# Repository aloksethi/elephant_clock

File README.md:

# elephant_clock
four digit clock

## Hardware
* two 7-seg displays for hours and two 7-seg displays for minutes.
* two switches along with debounce ckt.
* one green LED in middle of hours and minutes segments.
* rpi-pico is the brains.

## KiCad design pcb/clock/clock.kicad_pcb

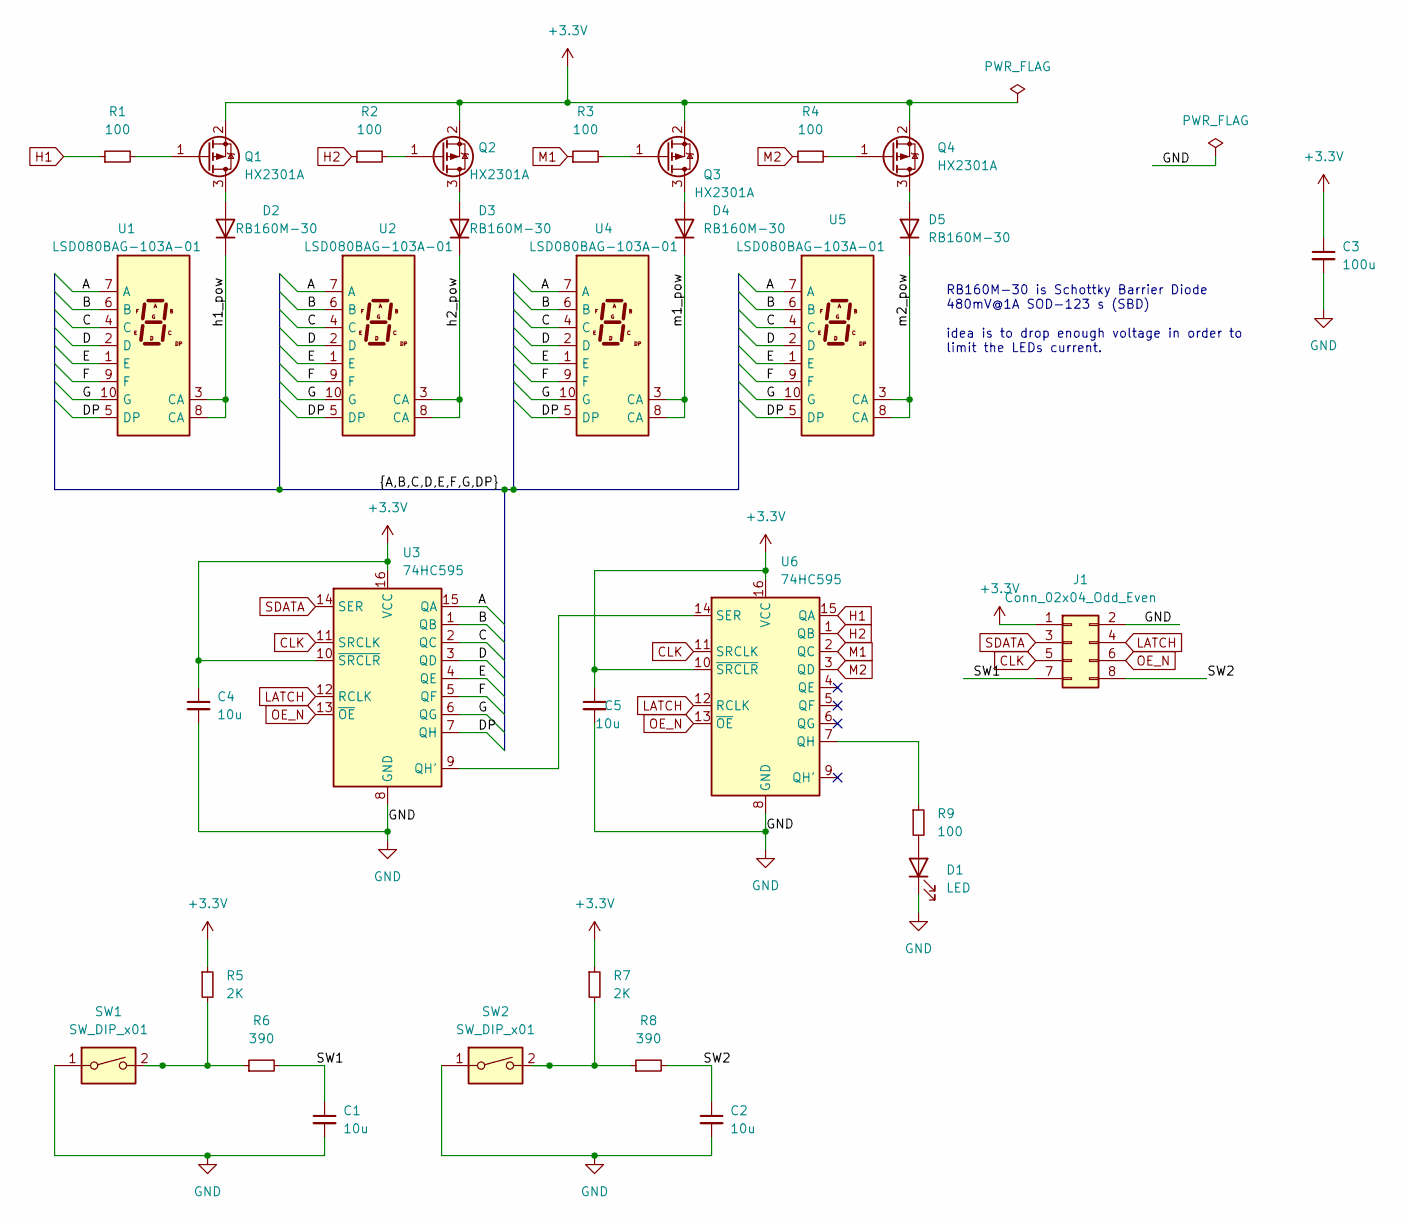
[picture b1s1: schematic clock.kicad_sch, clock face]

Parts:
C1, C2, C4, C5: 10u; C_0805_2012Metric_Pad1.18x1.45mm_HandSolder
C3: 100u; CP_Elec_8x10.5
D1: LED; LED_0805_2012Metric_Pad1.15x1.40mm_HandSolder
D2, D3, D4, D5: RB160M-30; D_SOD-123
J1: Conn_02x04_Odd_Even; PinHeader_2x04_P2.54mm_Vertical_SMD
Q1, Q2, Q3, Q4: HX2301A; SOT-23_Handsoldering
R1, R2, R3, R4: 100; R_0603_1608Metric_Pad0.98x0.95mm_HandSolder
R5, R7: 2K; R_0805_2012Metric_Pad1.20x1.40mm_HandSolder
R6, R8: 390; R_0805_2012Metric_Pad1.20x1.40mm_HandSolder
R9: 100; R_0805_2012Metric_Pad1.20x1.40mm_HandSolder
SW1, SW2: SW_DIP_x01; SW_SPST_lcsc_c174049
U1, U2, U4, U5: LSD080BAG-103A-01; 7SegmentLED_lsd080bag-103a
U3: 74HC595; SOIC-16_3.9x9.9mm_P1.27mm_handsolder
U6: 74HC595; SOIC-16_3.9x9.9mm_P1.27mm

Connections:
+3V3: C3.1, C4.1, C5.1, J1.1, Q1.2 (S), Q2.2 (S), Q3.2 (S), Q4.2 (S), R5.1, R7.1, U3.10 (~SRCLR), U3.16 (VCC), U6.10 (~SRCLR), U6.16 (VCC)
/A: U1.7 (A), U2.7 (A), U3.15 (QA), U4.7 (A), U5.7 (A)
/B: U1.6 (B), U2.6 (B), U3.1 (QB), U4.6 (B), U5.6 (B)
/C: U1.4 (C), U2.4 (C), U3.2 (QC), U4.4 (C), U5.4 (C)
/D: U1.2 (D), U2.2 (D), U3.3 (QD), U4.2 (D), U5.2 (D)
/DP: U1.5 (DP), U2.5 (DP), U3.7 (QH), U4.5 (DP), U5.5 (DP)
/E: U1.1 (E), U2.1 (E), U3.4 (QE), U4.1 (E), U5.1 (E)
/F: U1.9 (F), U2.9 (F), U3.5 (QF), U4.9 (F), U5.9 (F)
/G: U1.10 (G), U2.10 (G), U3.6 (QG), U4.10 (G), U5.10 (G)
/SW1: C1.1, J1.7, R6.2
/SW2: C2.1, J1.8, R8.2
/h1_pow: D2.1 (K), U1.3 (CA), U1.8 (CA)
/h2_pow: D3.1 (K), U2.3 (CA), U2.8 (CA)
/m1_pow: D4.1 (K), U4.3 (CA), U4.8 (CA)
/m2_pow: D5.1 (K), U5.3 (CA), U5.8 (CA)
CLK: J1.5, U3.11 (SRCLK), U6.11 (SRCLK)
GND: C1.2, C2.2, C3.2, C4.2, C5.2, D1.1 (K), J1.2, SW1.1, SW2.1, U3.8 (GND), U6.8 (GND)
H1: R1.1, U6.15 (QA)
H2: R2.1, U6.1 (QB)
LATCH: J1.4, U3.12 (RCLK), U6.12 (RCLK)
M1: R3.1, U6.2 (QC)
M2: R4.1, U6.3 (QD)
unnamed: D1.2 (A), R9.2
unnamed: Q1.1 (G), R1.2
unnamed: D2.2 (A), Q1.3 (D)
unnamed: Q2.1 (G), R2.2
unnamed: D3.2 (A), Q2.3 (D)
unnamed: Q3.1 (G), R3.2
unnamed: D4.2 (A), Q3.3 (D)
unnamed: Q4.1 (G), R4.2
unnamed: D5.2 (A), Q4.3 (D)
unnamed: R5.2, R6.1, SW1.2
unnamed: R7.2, R8.1, SW2.2
unnamed: R9.1, U6.7 (QH)
unnamed: U3.9 (QH'), U6.14 (SER)
OE_N: J1.6, U3.13 (~OE), U6.13 (~OE)
SDATA: J1.3, U3.14 (SER)

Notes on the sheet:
RB160M-30 is Schottky Barrier Diode 480mV@1A SOD-123 s (SBD) idea is to drop enough voltage in order to limit the LEDs current.

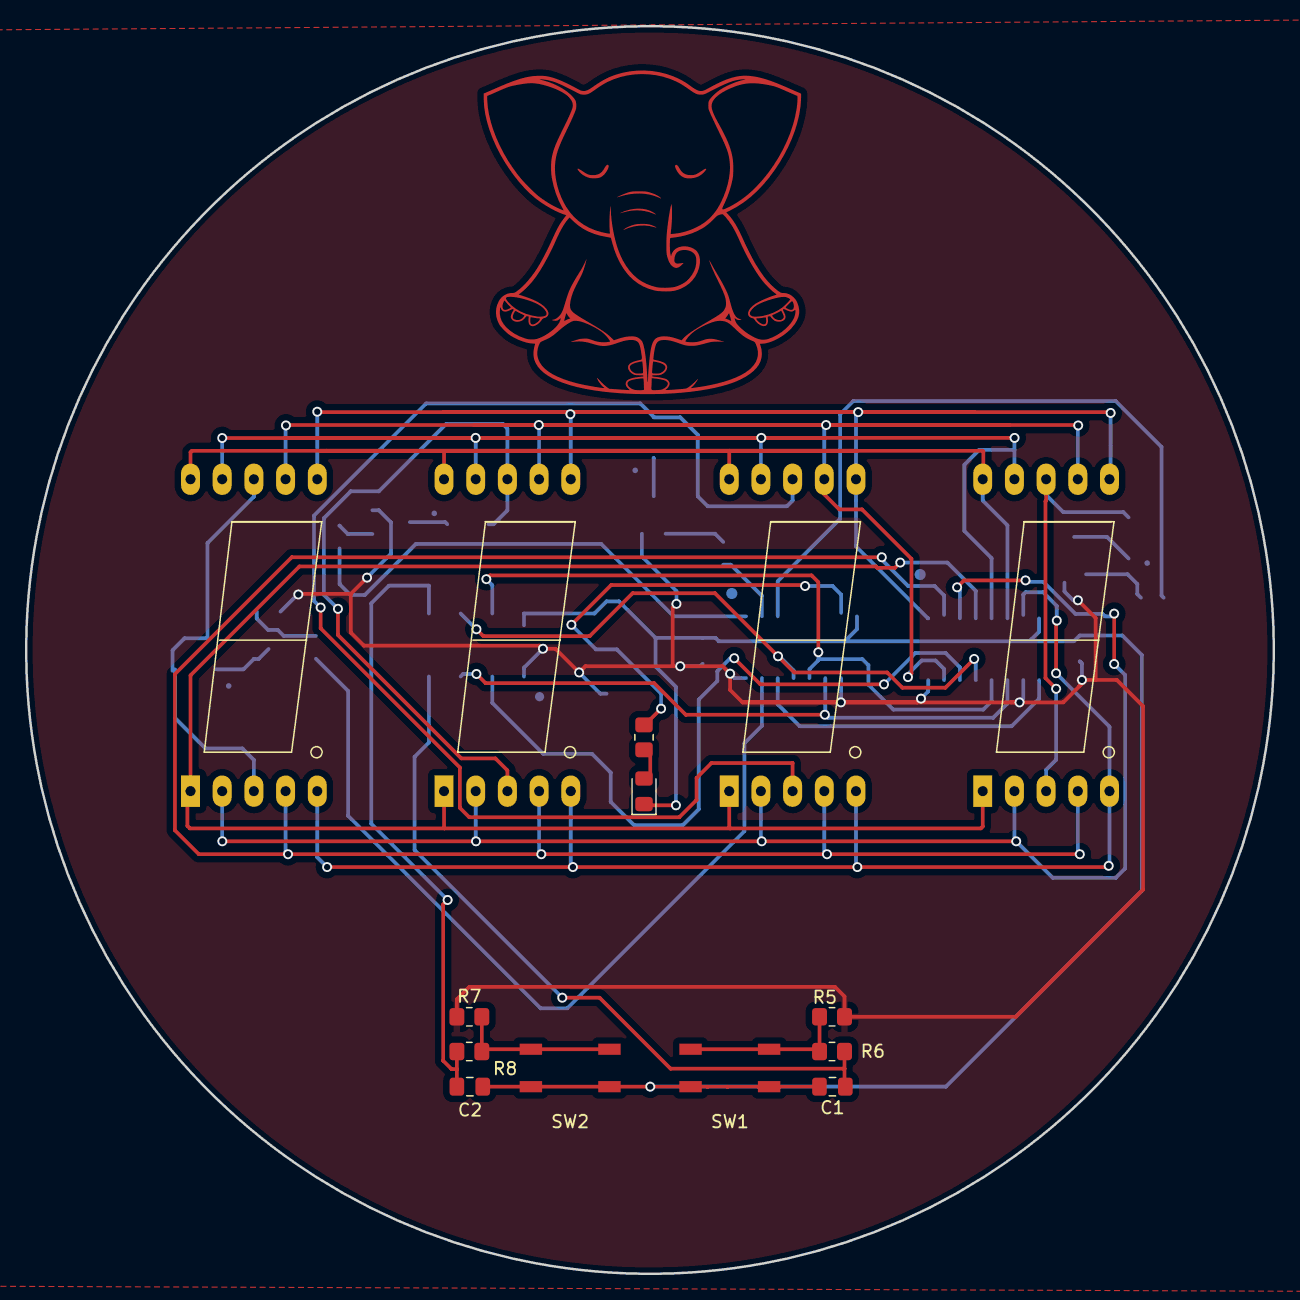
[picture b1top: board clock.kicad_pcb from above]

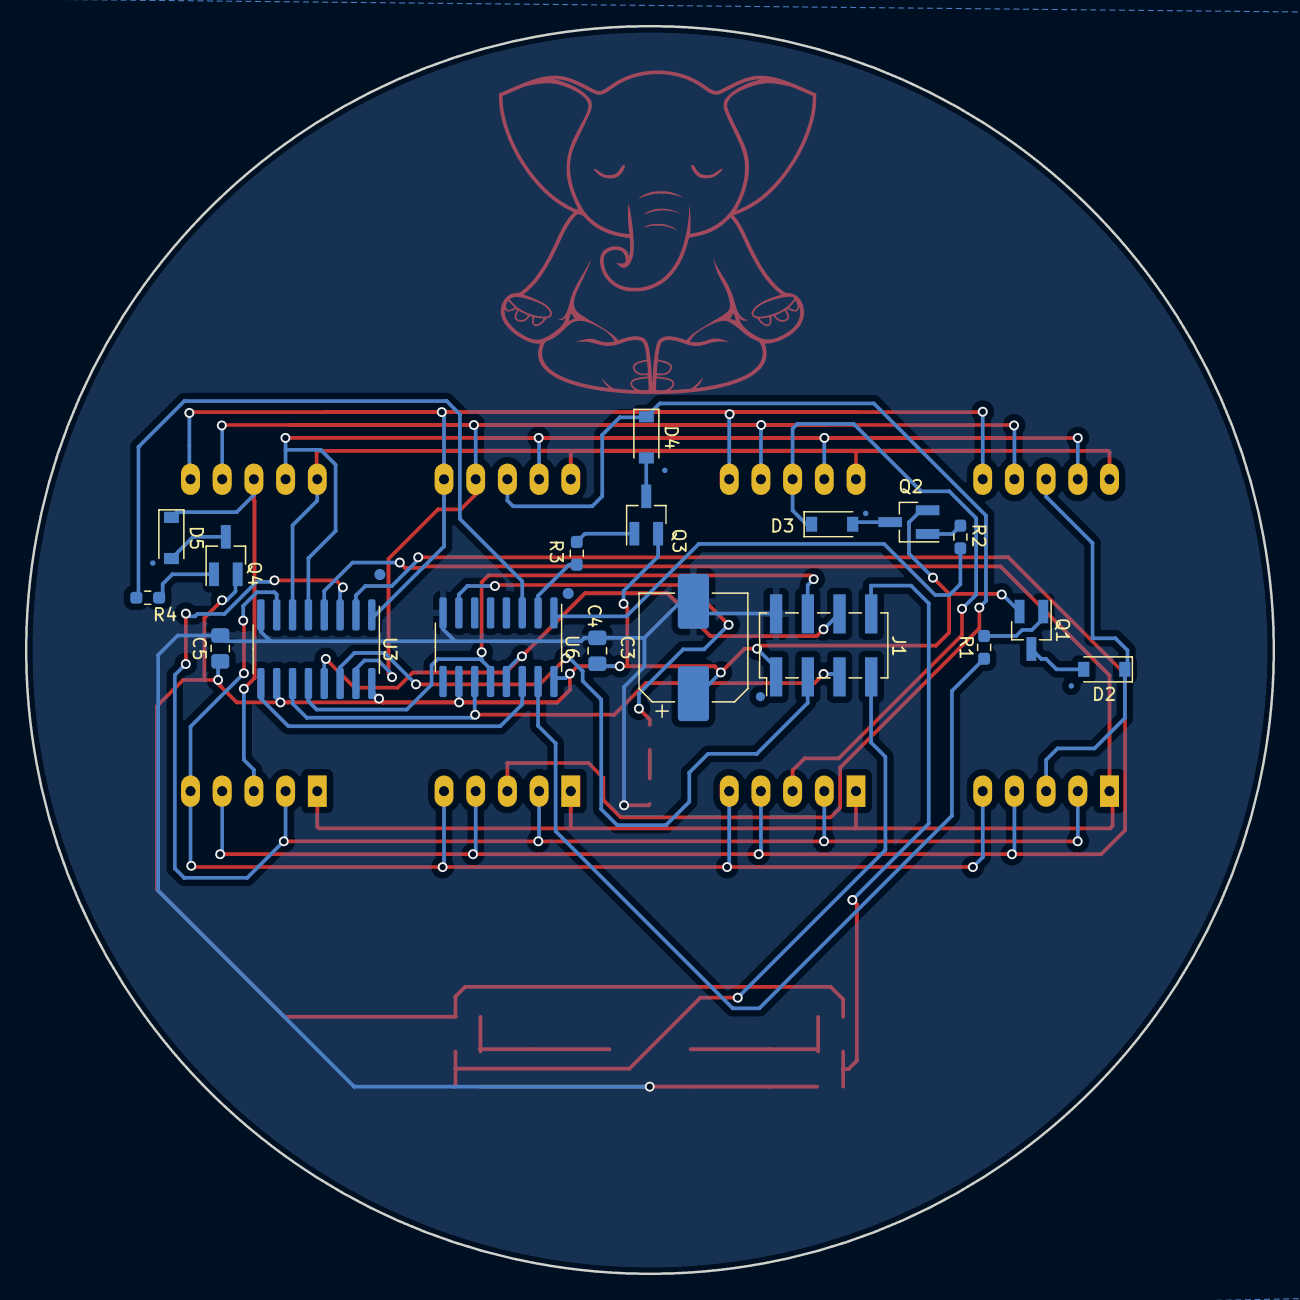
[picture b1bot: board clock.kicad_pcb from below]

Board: 2 copper layers, 100.0 x 100.0 mm, 32 parts (18 on the bottom side), 37 nets.

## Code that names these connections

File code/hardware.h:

#ifndef __HARDHARE_H
#define __HARDWARE_H

// define the GPIO mappings
#define LATCH   7
#define OE_N    3
#define CLCK    4
#define SDATA   6

#define SW1     5
#define SW2     2

#define HR_HD_IDX   0
#define HR_LD_IDX   1
#define MIN_HD_IDX   2
#define MIN_LD_IDX   3
#define MAX_DIGITS  4


/* external RTC connections*/
#define EXT_RTC_I2C_DEV         (i2c0)
#define EXT_RTC_I2C_ADDRESS     (0x68)
#define EXT_RTC_I2C_BAUDRATE    (100000)
#define EXT_RTC_I2C_SDA_PIN     (16)
#define EXT_RTC_I2C_SCL_PIN     (17)

/* DS3231 internal registers*/
#define EXT_RTC_SEC_REG         (0x0)
#define EXT_RTC_MIN_REG         (0x1)
#define EXT_RTC_HR_REG          (0x2)
#define EXT_RTC_DOW_REG         (0x3)
#define EXT_RTC_DAY_REG         (0x4)
#define EXT_RTC_MON_REG         (0x5)
#define EXT_RTC_YR_REG          (0x6)

/* function definitions*/
void display_time(void);

#endif

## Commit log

2023-04-01 created an empty pcb
2023-04-01 started with schematic. still need buttons,power n other thigns.
2023-04-03 hopefully a complete schematic with footprints allocated
2023-04-04 fixed wrong symbol for the 7seg, D leg was shorted with E leg, added elephant logo. placement of 7 seg n switches
2023-04-15 added gerber files and bkup files
2023-04-15 first complete pcb of the clock
2023-05-07 blink example build
2023-06-15 new version. tried to fix the busg in v1
2023-06-15 grbs files for the 2nd version
2023-06-15 ttesting the delete
2023-07-11 able to display characters on the 4 digits
2023-07-31 basic clock code. no way to update the time yet
2023-07-31 switches and time setting fucntionality are working
2025-01-01 gdb init file
2025-01-01 added support of ds3231 module over i2c
